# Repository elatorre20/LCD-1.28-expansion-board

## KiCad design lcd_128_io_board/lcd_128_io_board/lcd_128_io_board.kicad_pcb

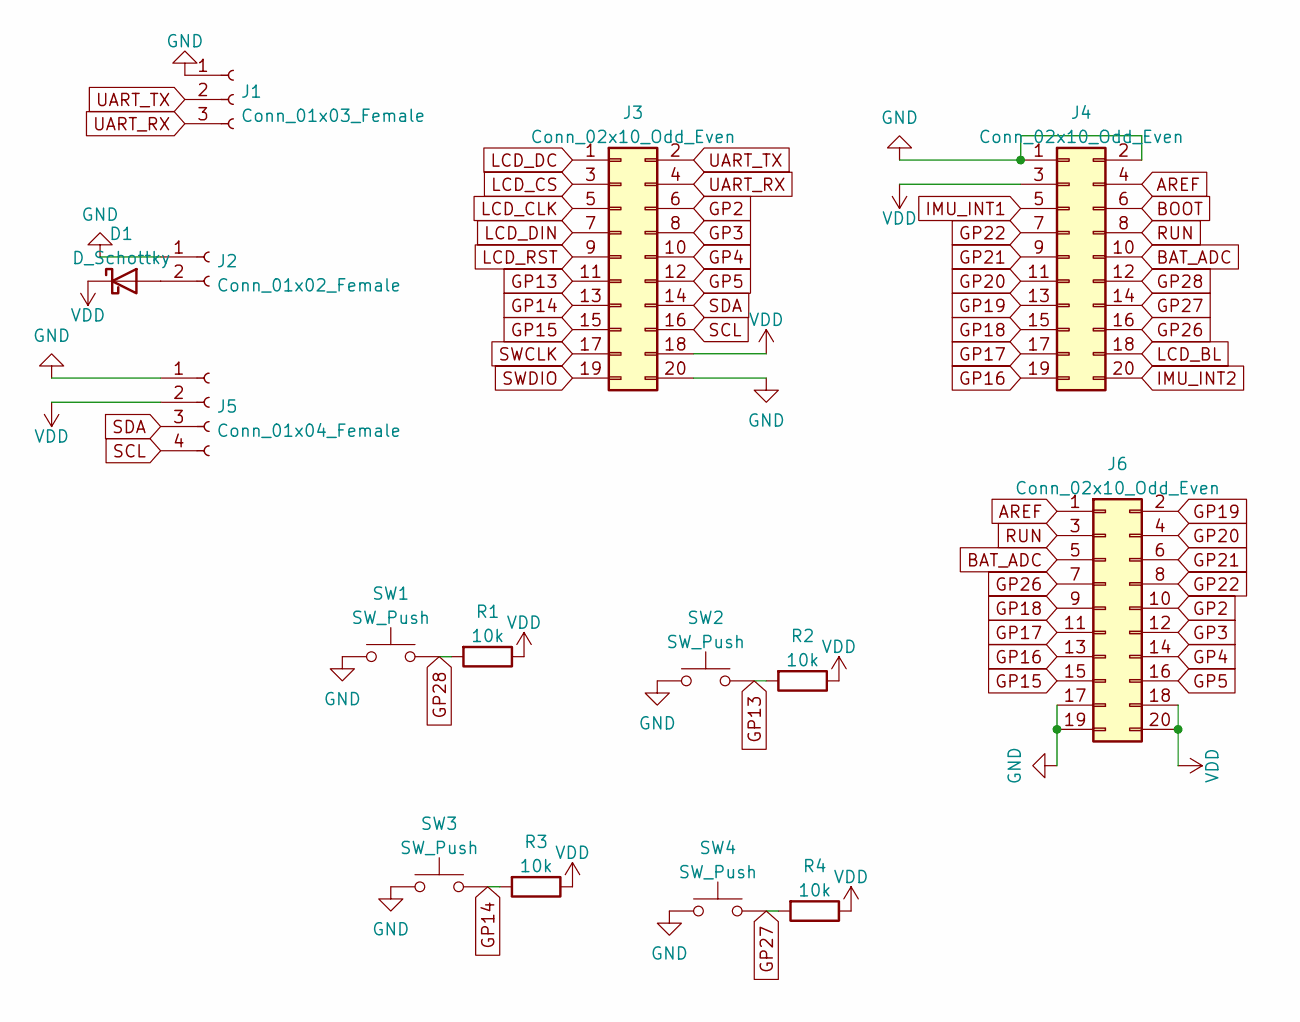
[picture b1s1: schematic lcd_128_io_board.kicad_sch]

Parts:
D1: D_Schottky; D_DO-15_P10.16mm_Horizontal
J1: Conn_01x03_Female; PinHeader_1x03_P2.54mm_Vertical
J2: Conn_01x02_Female; PinHeader_1x02_P2.54mm_Vertical
J3, J4: Conn_02x10_Odd_Even; PinHeader_2x10_P1.27mm_Vertical
J5: Conn_01x04_Female; PinHeader_1x04_P2.54mm_Vertical
J6: Conn_02x10_Odd_Even; PinHeader_2x10_P2.54mm_Vertical
R1, R2, R3, R4: 10k; R_Axial_DIN0411_L9.9mm_D3.6mm_P12.70mm_Horizontal
SW1, SW2, SW3, SW4: SW_Push; SW_PUSH_6mm

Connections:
AREF: J4.4, J6.1
BAT_ADC: J4.10, J6.5
BOOT: J4.6
GND: J1.1, J2.1, J3.20, J4.1, J4.2, J5.1, J6.17, J6.19, SW1.1, SW2.1, SW3.1, SW4.1
GP2: J3.6, J6.10
GP3: J3.8, J6.12
GP4: J3.10, J6.14
GP5: J3.12, J6.16
GP13: J3.11, R2.2, SW2.2
GP14: J3.13, R3.2, SW3.2
GP15: J3.15, J6.15
GP16: J4.19, J6.13
GP17: J4.17, J6.11
GP18: J4.15, J6.9
GP19: J4.13, J6.2
GP20: J4.11, J6.4
GP21: J4.9, J6.6
GP22: J4.7, J6.8
GP26: J4.16, J6.7
GP27: J4.14, R4.2, SW4.2
GP28: J4.12, R1.2, SW1.2
IMU_INT1: J4.5
IMU_INT2: J4.20
LCD_BL: J4.18
LCD_CLK: J3.5
LCD_CS: J3.3
LCD_DC: J3.1
LCD_DIN: J3.7
LCD_RST: J3.9
unnamed: D1.2 (A), J2.2
RUN: J4.8, J6.3
SCL: J3.16, J5.4
SDA: J3.14, J5.3
SWCLK: J3.17
SWDIO: J3.19
UART_RX: J1.3, J3.4
UART_TX: J1.2, J3.2
VDD: D1.1 (K), J3.18, J4.3, J5.2, J6.18, J6.20, R1.1, R2.1, R3.1, R4.1

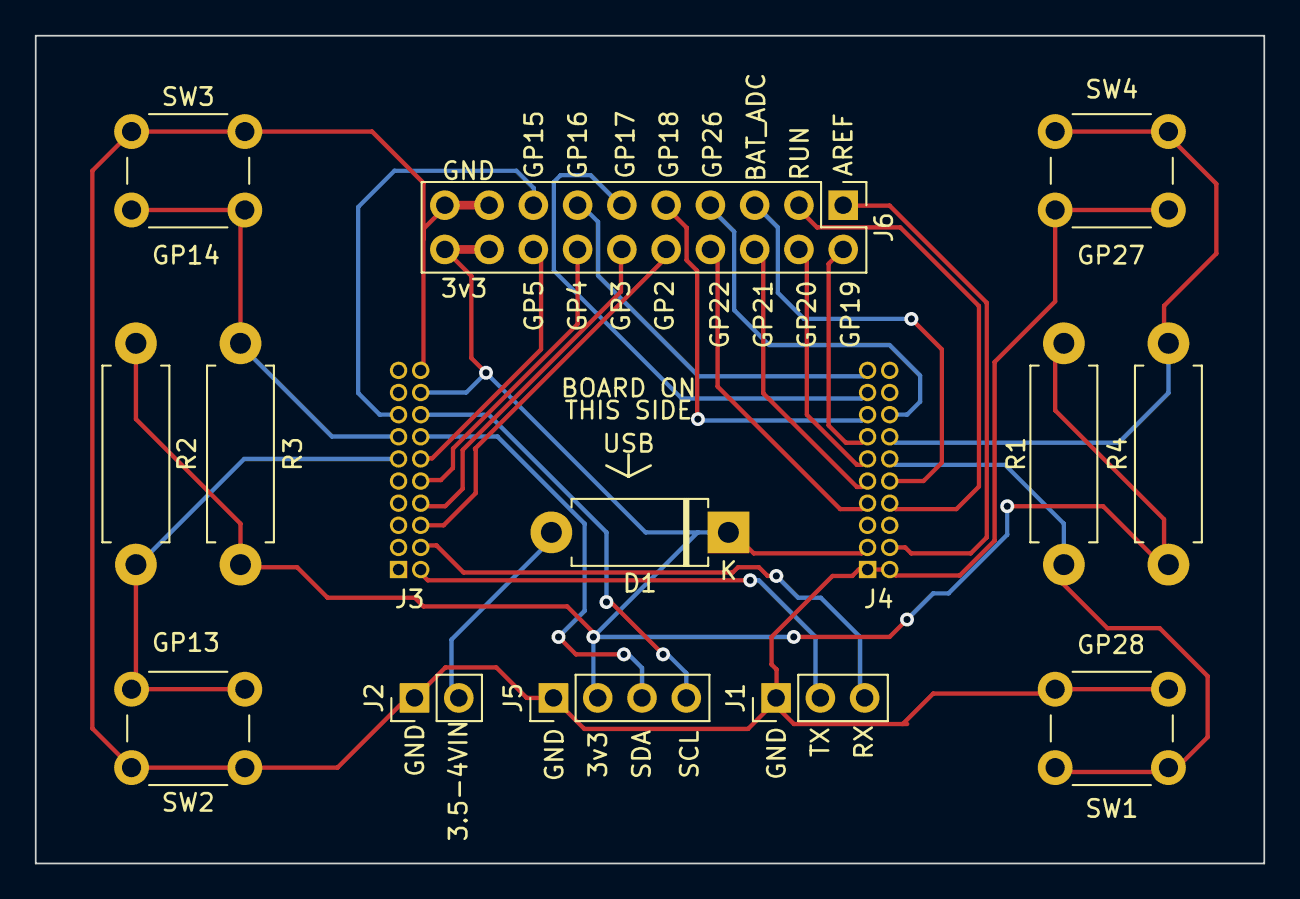
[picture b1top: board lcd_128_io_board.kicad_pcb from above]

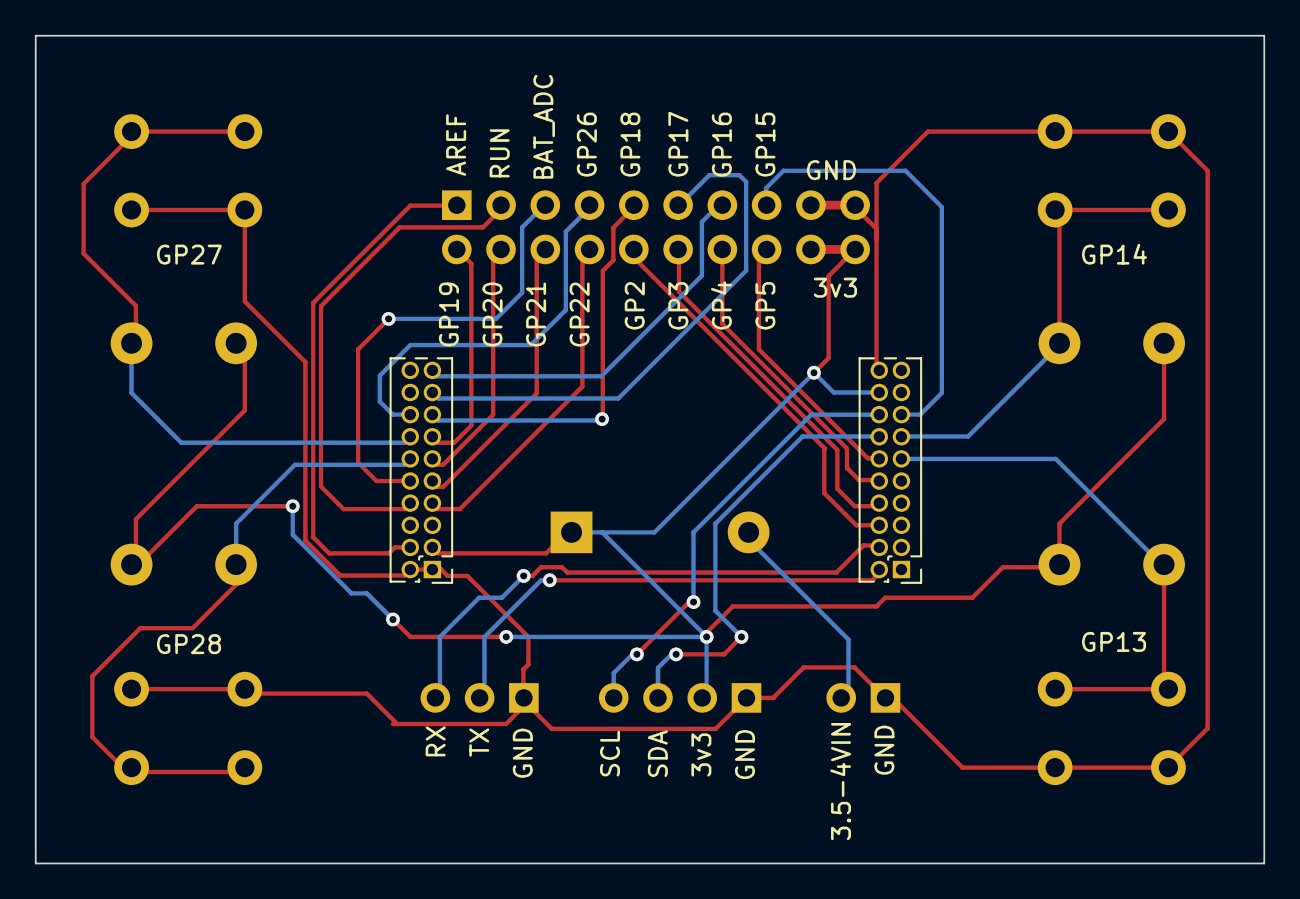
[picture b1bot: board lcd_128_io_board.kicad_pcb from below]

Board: 2 copper layers, 70.5 x 47.5 mm, 15 parts (2 on the bottom side), 27 nets.

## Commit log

2023-09-22 initial upload
2023-09-26 layout almost finished
    Moved around a few pins for better routing
2023-09-26 layout almost done
    Layout finished, must correct for incorrect orientation of small-pitch headers
2023-10-05 plotted and ordered
2023-12-04 Rev 2 board
    Fixed misalignment in 1.27mm GPIO headers. Fixed silkscreen typos. Added silkscreen assembly directions.
